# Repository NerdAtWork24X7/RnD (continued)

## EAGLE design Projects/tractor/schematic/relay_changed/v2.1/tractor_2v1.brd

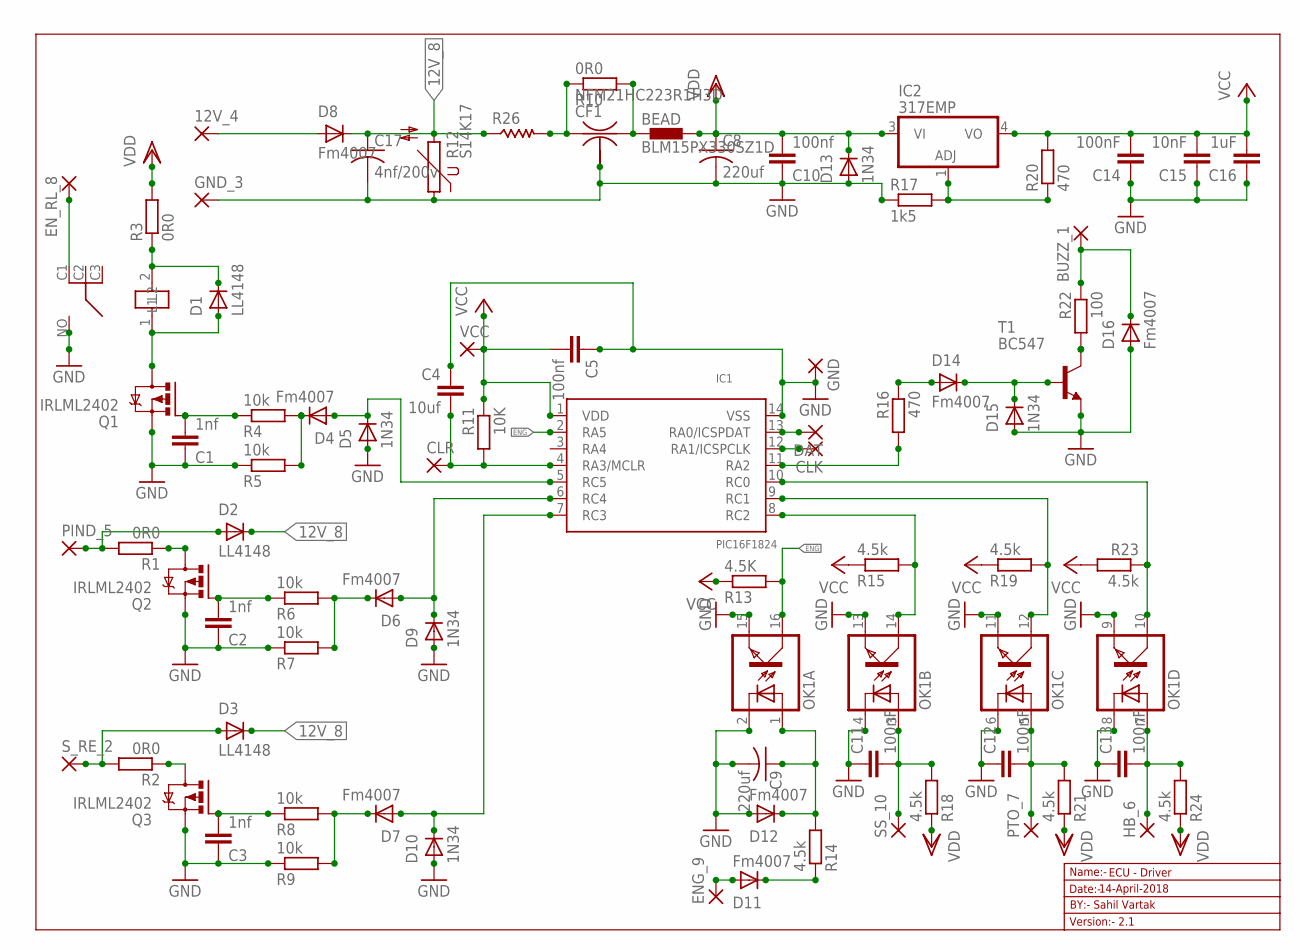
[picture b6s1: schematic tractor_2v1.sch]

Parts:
12V_4: 2,54/1,1
BEAD: BLM15PX330SZ1D; 0402
BUZZ_1: 2,54/1,1
C1, C2, C3: 1nf; C0603
C4: 10uf; C0603
C5, C10: 100nf; C0603
C8, C9: 220uf; C025-025X050
C11, C12, C13, C14: 100nF; C0603
C15: 10nF; C0603
C16: 1uF; C0603
C17: 4nf/200v; C050-045X075
CF1: NFM21HC223R1H3D; NFM3DC
CLK: 1,6/0,8
CLR: 1,6/0,8
D1, D2, D3: LL4148; SMA-DO214AC
D4, D6, D7, D8, D11, D12, D14, D16: Fm4007; SMA-DO214AC
D5, D9, D10, D13, D15: 1N34; SMA-DO214AC
DAT: 1,6/0,8
ENG_9: 2,54/1,1
EN_RL_8: 2,54/1,1
GND: 1,6/0,8
GND_3: 2,54/1,1
HB_6: 2,54/1,1
IC1: PIC16F1824; SO-14
IC2: 317EMP; SOT223
K1: RL703
OK1: TLP283-4; MINI-FLAT-16
PIND_5: 2,54/1,1
PTO_7: 2,54/1,1
Q1, Q2, Q3: IRLML2402; MICRO3
R1, R2, R3, R10: 0R0; R0603
R4, R5, R6, R7, R8, R9: 10k; R0603
R11: 10K; R0603
R12: S14K17
R13: 4.5K; R0603
R14, R15, R18, R19, R21, R23, R24: 4.5k; R0603
R16, R20: 470; R0603
R17: 1k5; R0603
R22: 100; R0603
R26: R-US_WSC2515; WSC2515
SS_10: 2,54/1,1
S_RE_2: 2,54/1,1
T1: BC547; TO92
VCC: 1,6/0,8

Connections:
12V_8: C17.1, D2.K (C), D3.K (C), D8.K (C), R12.2, R26.1
BUZZ_4: BUZZ_1.1, D16.K (C), R22.1
ENG: IC1.2 (RA5), OK1.16 (COL), R13.2
GND: C1.1, C2.1, C3.1, C4.1, C5.1, C8.2, C9.2, C10.1, C11.1, C12.1, C13.1, C14.1, C15.1, C16.1, C17.2, CF1.2@1 (2), D5.A, D9.A, D10.A, D12.A, D13.A, D15.A, D16.A, GND.1, GND_3.1, IC1.14 (VSS), K1.NO, OK1.2 (C), OK1.4 (C), OK1.6 (C), OK1.8 (C), OK1.9 (EMIT), OK1.11 (EMIT), OK1.13 (EMIT), OK1.15 (EMIT), Q1.2 (S), Q2.2 (S), Q3.2 (S), R5.1, R7.1, R9.1, R12.1, R17.1, T1.1 (E)
unnamed: D11.K (C), R14.1
unnamed: IC1.10 (RC0), OK1.10 (COL), R23.1
unnamed: D1.A, K1.1 (L2), Q1.3 (D)
unnamed: C2.2, Q2.1 (G), R6.1
unnamed: CF1.1, R10.1, R26.2
unnamed: DAT.1, IC1.13 (RA0/ICSPDAT)
unnamed: CLK.1, IC1.12 (RA1/ICSPCLK)
unnamed: D1.K (C), K1.2 (L1), R3.1
unnamed: IC2.1 (ADJ), R17.2, R20.1
unnamed: BEAD.1, CF1.3, R10.2
unnamed: D14.A, R16.1
unnamed: D4.A, D5.K (C), IC1.5 (RC5)
unnamed: C3.2, Q3.1 (G), R8.1
unnamed: D7.K (C), R8.2, R9.2
unnamed: IC1.11 (RA2), R16.2
unnamed: Q3.3 (D), R2.1
unnamed: D11.A, ENG_9.1
unnamed: C9.1, D12.K (C), OK1.1 (A), R14.2
unnamed: D6.K (C), R6.2, R7.2
unnamed: D2.A, PIND_5.1, R1.2
unnamed: D6.A, D9.K (C), IC1.6 (RC4)
unnamed: D3.A, R2.2, S_RE_2.1
unnamed: Q2.3 (D), R1.1
unnamed: 12V_4.1, D8.A
unnamed: D7.A, D10.K (C), IC1.7 (RC3)
unnamed: C1.2, Q1.1 (G), R4.1
unnamed: D4.K (C), R4.2, R5.2
unnamed: C11.2, OK1.3 (A), R18.2, SS_10.1
unnamed: C12.2, OK1.5 (A), PTO_7.1, R21.2
unnamed: C13.2, HB_6.1, OK1.7 (A), R24.2
unnamed: IC1.9 (RC1), OK1.12 (COL), R19.2
unnamed: IC1.8 (RC2), OK1.14 (COL), R15.2
unnamed: C4.2, CLR.1, IC1.4 (RA3/MCLR), R11.2
unnamed: D14.K (C), D15.K (C), T1.2 (B)
unnamed: R22.2, T1.3 (C)
R_3: EN_RL_8.1, K1.C1
VCC: C5.2, C14.2, C15.2, C16.2, IC1.1 (VDD), IC2.4 (VO), R11.1, R13.1, R15.1, R19.1, R20.2, R23.2, VCC.1
VDD: BEAD.2, C8.1, C10.2, D13.K (C), IC2.3 (VI), R3.2, R18.1, R21.1, R24.1

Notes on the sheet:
Name:-
Version:- 2.1
Date:-
ECU - Driver
BY:- Sahil Vartak
14-April-2018

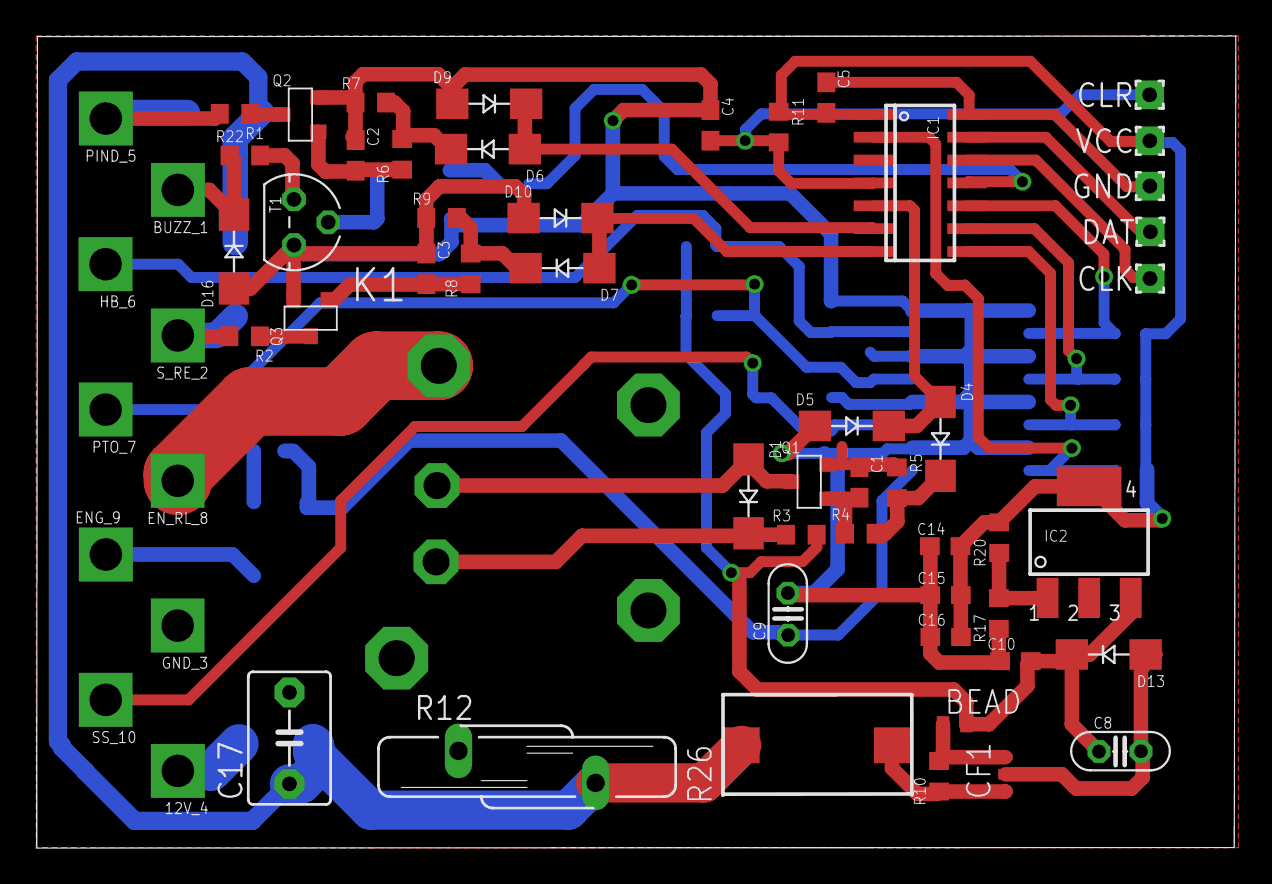
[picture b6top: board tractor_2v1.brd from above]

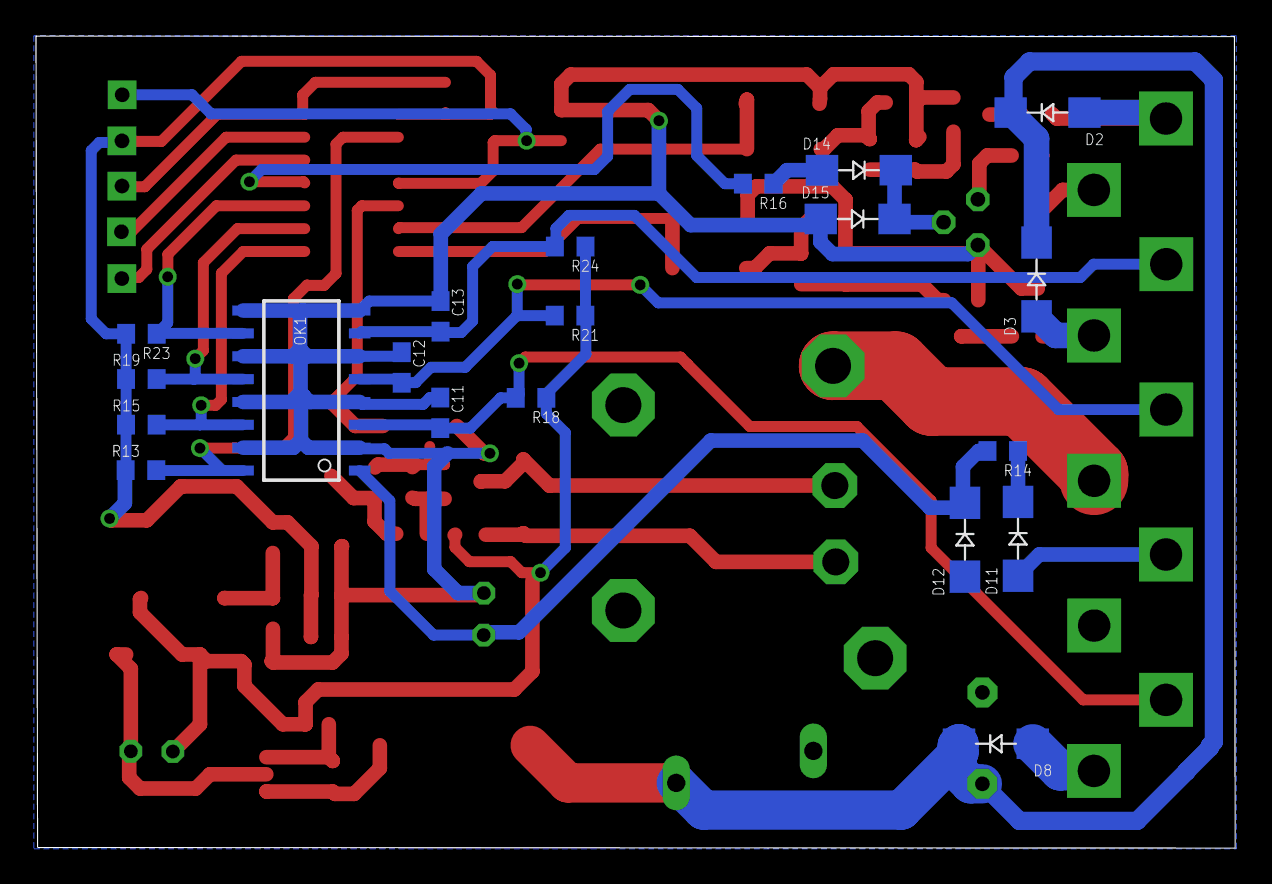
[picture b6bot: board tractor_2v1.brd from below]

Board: 2 copper layers, 66.7 x 45.1 mm, 81 parts (21 on the bottom side), 42 nets.
